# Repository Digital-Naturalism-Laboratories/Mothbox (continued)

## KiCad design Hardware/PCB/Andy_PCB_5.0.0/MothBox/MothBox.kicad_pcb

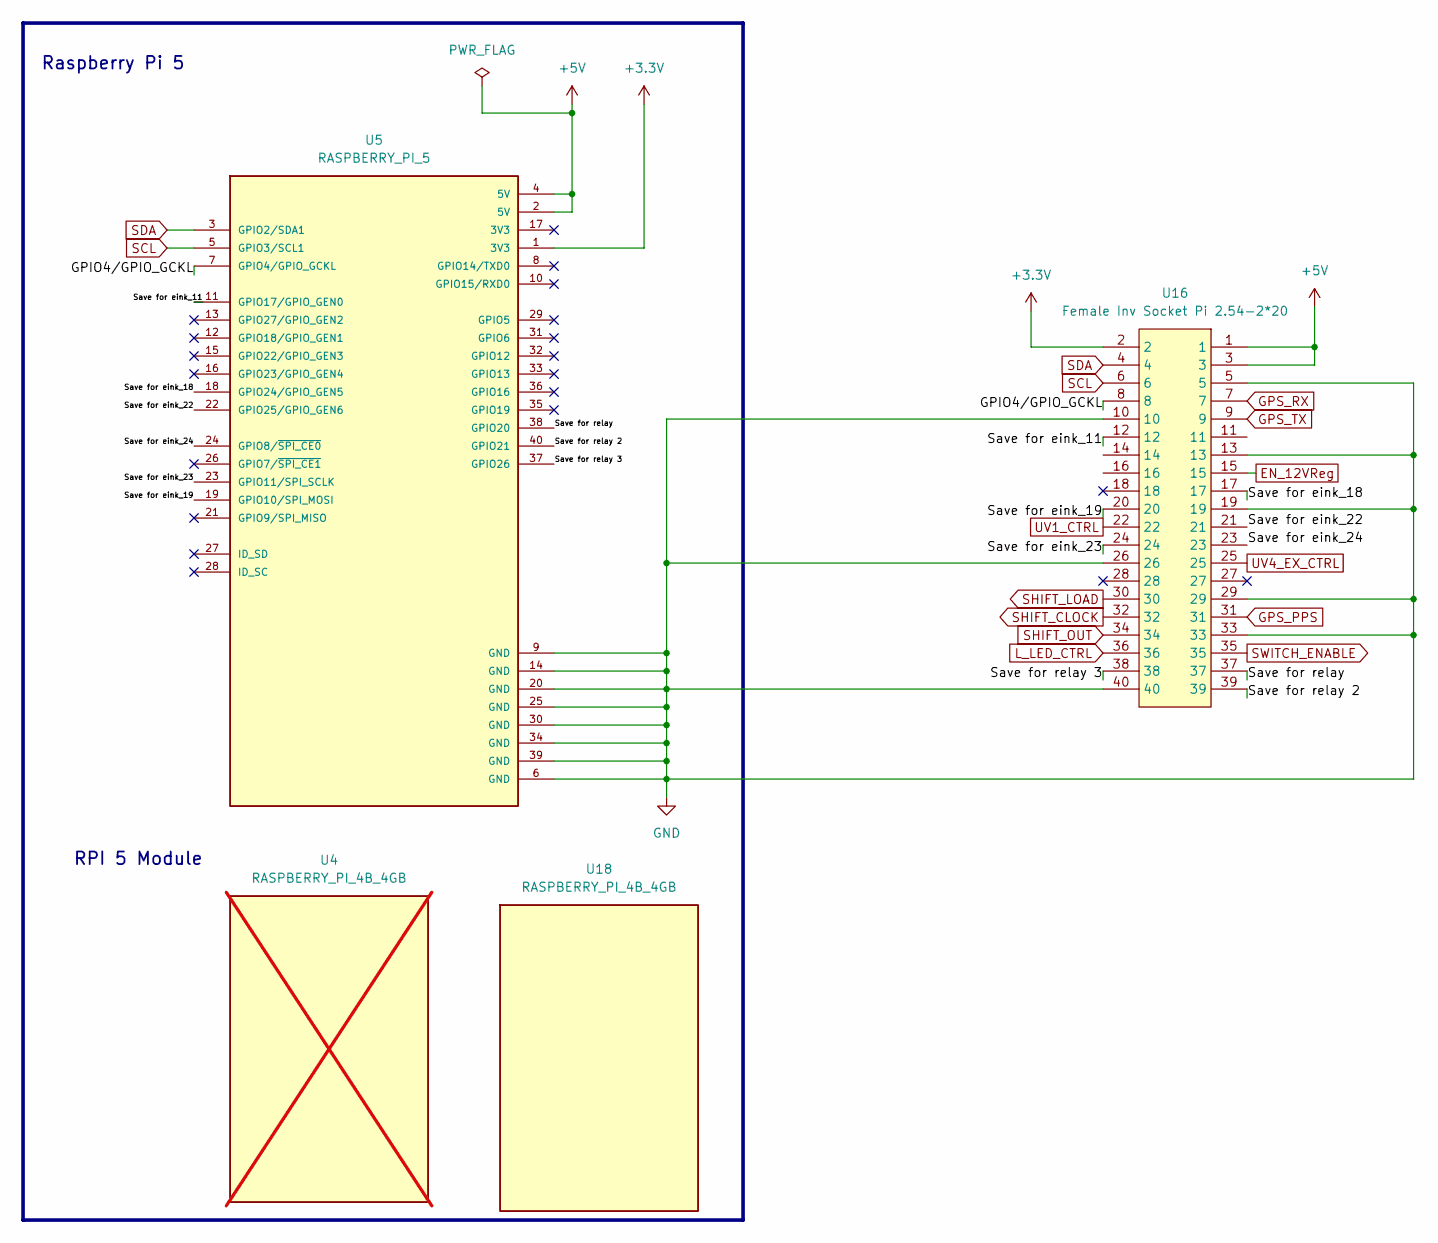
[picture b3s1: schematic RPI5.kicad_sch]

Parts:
U4: RASPBERRY_PI_4B_4GB; MODULE_RASPBERRY_PI_4B_4GB; PARTREV 4; Digikey Part No SC1113; not fitted
U5: RASPBERRY_PI_5; EPAPER_PinHeader_2x20_P2.54mm_Vertical; LCSC Part no C5224014
U16: Female Inv Socket Pi 2.54-2*20; HDR-TH_40P-P2.54-H-F-R2-C20-W8.5; LCSC Part C2897440
U18: RASPBERRY_PI_4B_4GB; MODULE_RASPBERRY_PI_4B_4GB_Sideways; PARTREV 4; Digikey Part No SC1113

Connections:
+3.3V: U5.1 (3V3), U16.2; also elsewhere on the board
+5V: U5.2 (5V), U5.4 (5V), U16.1, U16.3; also elsewhere on the board
/RPI5/GPIO4/GPIO_GCKL: U5.7 (GPIO4/GPIO_GCKL), U16.8
/RPI5/Save for eink_11: U5.11 (GPIO17/GPIO_GEN0), U16.12
/RPI5/Save for eink_18: U5.18 (GPIO24/GPIO_GEN5), U16.17
/RPI5/Save for eink_19: U5.19 (GPIO10/SPI_MOSI), U16.20
/RPI5/Save for eink_22: U5.22 (GPIO25/GPIO_GEN6), U16.21
/RPI5/Save for eink_23: U5.23 (GPIO11/SPI_SCLK), U16.24
/RPI5/Save for eink_24: U5.24 (GPIO8/~SPI_CE0), U16.23
/RPI5/Save for relay: U5.38 (GPIO20), U16.37
/RPI5/Save for relay 2: U5.40 (GPIO21), U16.39
/RPI5/Save for relay 3: U5.37 (GPIO26), U16.38
EN_12VReg: U16.15; also elsewhere on the board
GND: U5.6 (GND), U5.9 (GND), U5.14 (GND), U5.20 (GND), U5.25 (GND), U5.30 (GND), U5.34 (GND), U5.39 (GND), U16.5, U16.10, U16.13, U16.19, U16.26, U16.29, U16.33, U16.40; also elsewhere on the board
GPS_PPS: U16.31; also elsewhere on the board
GPS_RX: U16.7; also elsewhere on the board
GPS_TX: U16.9; also elsewhere on the board
L_LED_CTRL: U16.36; also elsewhere on the board
SCL: U5.5 (GPIO3/SCL1), U16.6; also elsewhere on the board
SDA: U5.3 (GPIO2/SDA1), U16.4; also elsewhere on the board
SHIFT_CLOCK: U16.32; also elsewhere on the board
SHIFT_LOAD: U16.30; also elsewhere on the board
SHIFT_OUT: U16.34; also elsewhere on the board
SWITCH_ENABLE: U16.35; also elsewhere on the board
UV1_CTRL: U16.22; also elsewhere on the board
UV4_EX_CTRL: U16.25; also elsewhere on the board

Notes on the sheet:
RPI 5 Module
Raspberry Pi 5

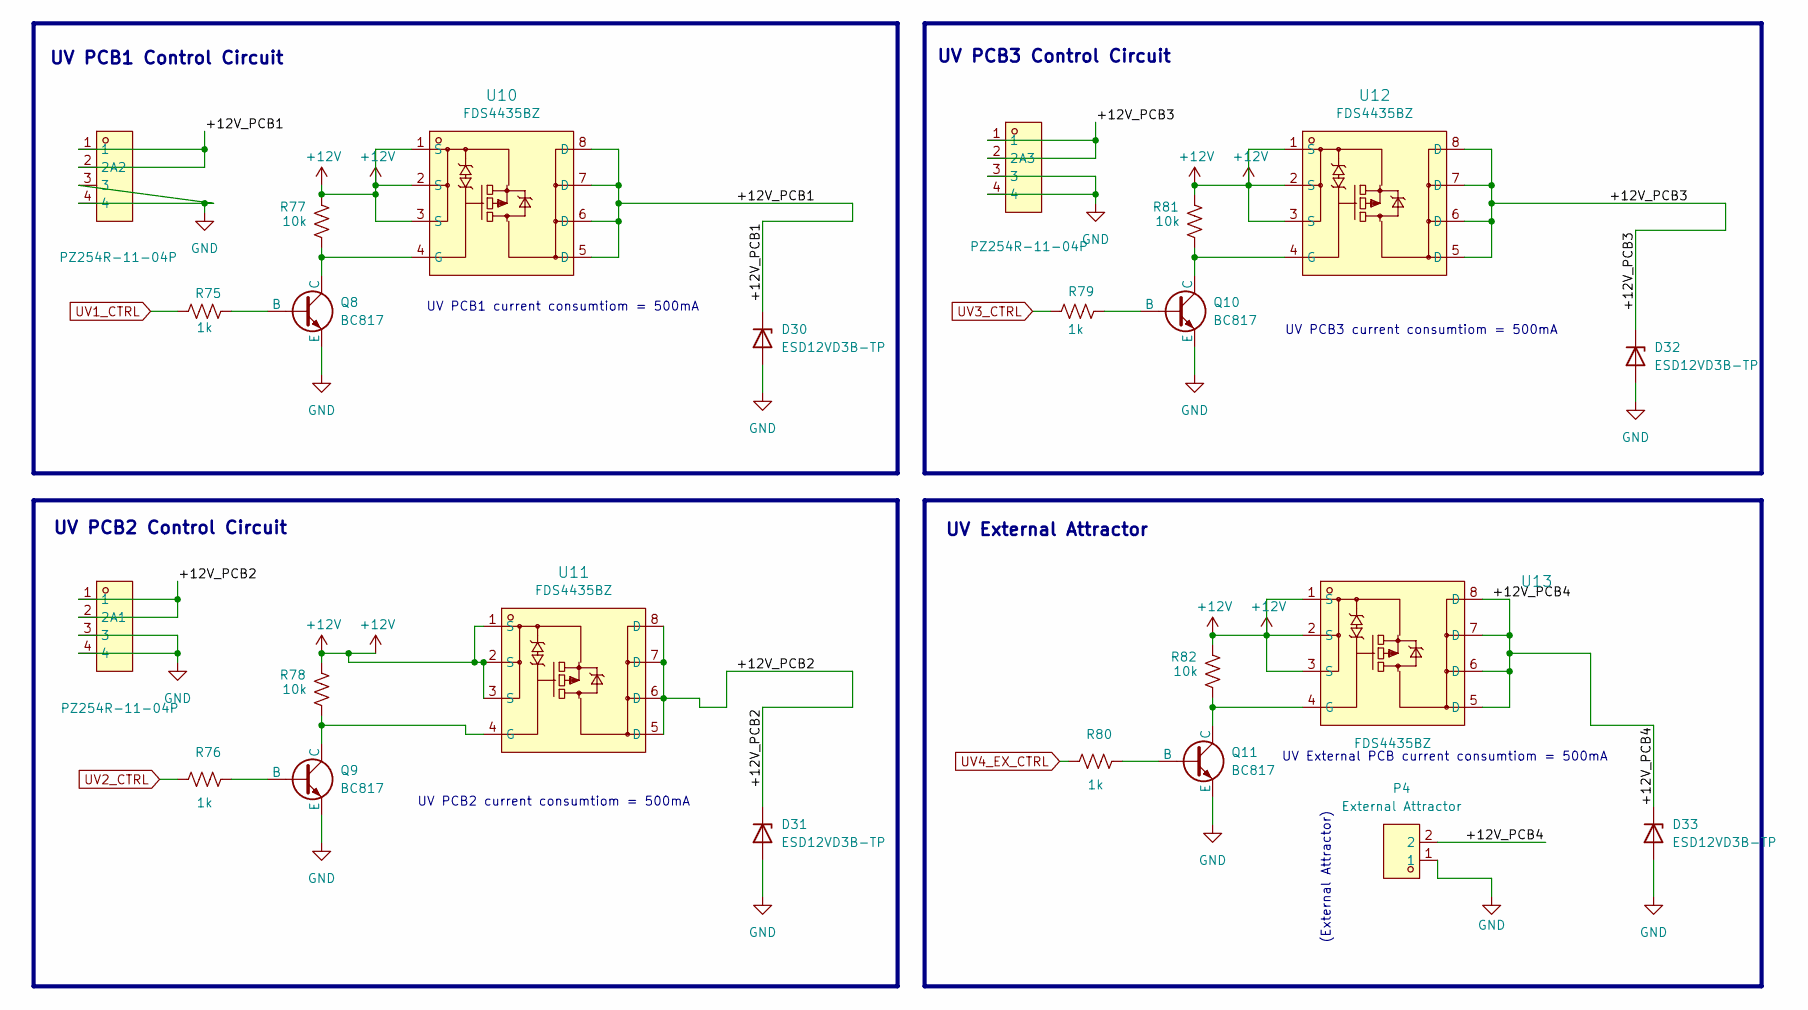
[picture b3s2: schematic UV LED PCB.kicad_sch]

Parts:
A1, A2, A3: PZ254R-11-04P; HDR-TH_4P-P2.54-H-M-W10.4; LCSC Part C492412
D30, D31, D32, D33: ESD12VD3B-TP; D_SOD-323; LCSC Part no C435886
P4: External Attractor; CONN-TH_2P-P5.08_DIBO_DB142R-5.08-2P; LCSC Part C2898709
Q8, Q9, Q10, Q11: BC817; SOT-23; LCSC Part no C39828
R75, R76, R79, R80: 1k; R_0805_2012Metric; LCSC Part no C95781
R77, R78, R81, R82: 10k; R_0805_2012Metric; LCSC Part no C84376
U10, U11, U12, U13: FDS4435BZ; SOIC-8_L5.0-W4.0-P1.27-LS6.0-BL; LCSC Part C23931

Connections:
+12V: R77.2, R78.2, R81.2, R82.2, U10.1 (S), U10.2 (S), U10.3 (S), U11.1 (S), U11.2 (S), U11.3 (S), U12.1 (S), U12.2 (S), U12.3 (S), U13.1 (S), U13.2 (S), U13.3 (S); also elsewhere on the board
/UV LED PCB/+12V_PCB1: A2.1, A2.2, D30.1 (K), U10.5 (D), U10.6 (D), U10.7 (D), U10.8 (D)
/UV LED PCB/+12V_PCB2: A1.1, A1.2, D31.1 (K), U11.5 (D), U11.6 (D), U11.7 (D), U11.8 (D)
/UV LED PCB/+12V_PCB3: A3.1, A3.2, D32.1 (K), U12.5 (D), U12.6 (D), U12.7 (D), U12.8 (D)
/UV LED PCB/+12V_PCB4: D33.1 (K), P4.2, U13.5 (D), U13.6 (D), U13.7 (D), U13.8 (D)
GND: A1.3, A1.4, A2.3, A2.4, A3.3, A3.4, D30.2 (A), D31.2 (A), D32.2 (A), D33.2 (A), P4.1, Q8.2 (E), Q9.2 (E), Q10.2 (E), Q11.2 (E); also elsewhere on the board
unnamed: Q8.1 (B), R75.1
unnamed: Q8.3 (C), R77.1, U10.4 (G)
unnamed: Q9.1 (B), R76.1
unnamed: Q9.3 (C), R78.1, U11.4 (G)
unnamed: Q10.1 (B), R79.1
unnamed: Q10.3 (C), R81.1, U12.4 (G)
unnamed: Q11.1 (B), R80.1
unnamed: Q11.3 (C), R82.1, U13.4 (G)
UV1_CTRL: R75.2; also elsewhere on the board
UV2_CTRL: R76.2
UV3_CTRL: R79.2
UV4_EX_CTRL: R80.2; also elsewhere on the board

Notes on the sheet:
UV External Attractor
(External Attractor)
UV PCB1 Control Circuit
UV PCB3 Control Circuit
UV PCB1 current consumtiom = 500mA
UV PCB2 current consumtiom = 500mA
UV PCB3 current consumtiom = 500mA
UV PCB2 Control Circuit
UV External PCB current consumtiom = 500mA

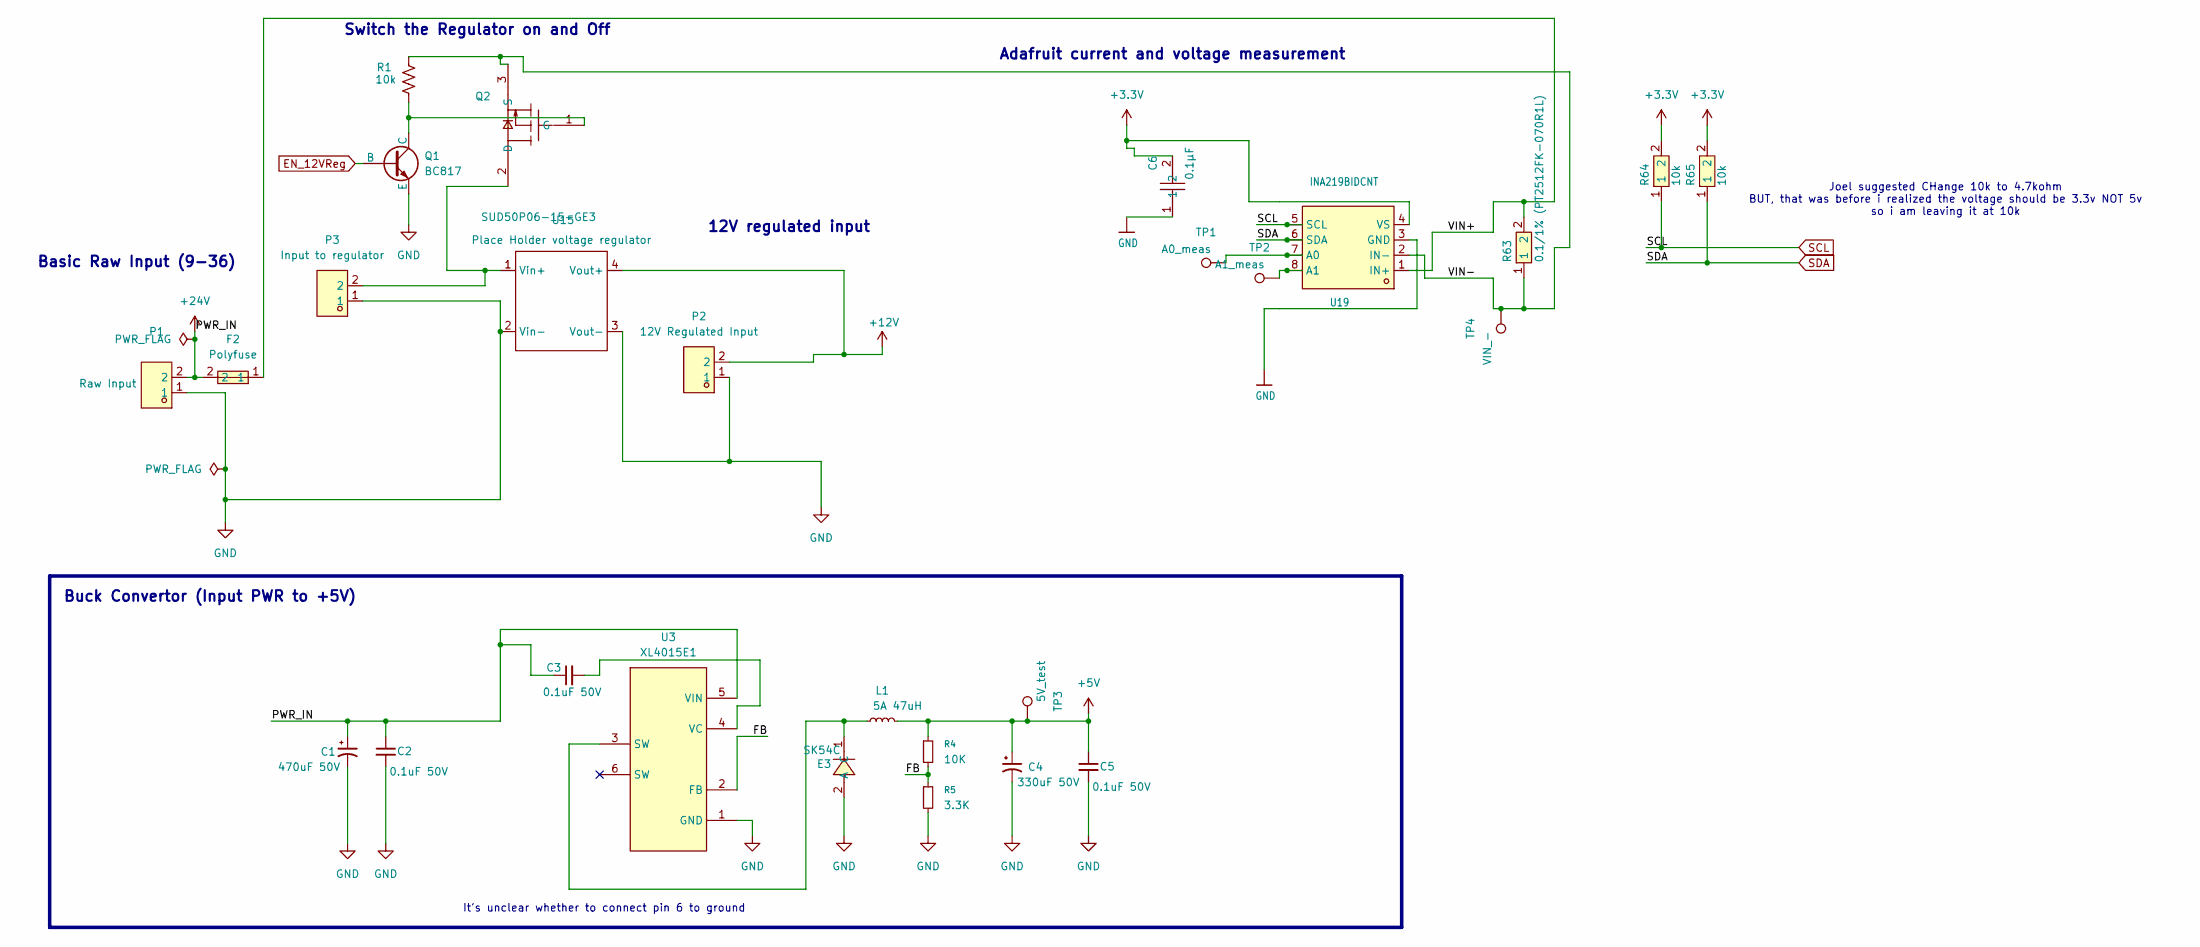
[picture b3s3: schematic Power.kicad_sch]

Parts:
C1: 470uF 50V; CP_Elec_10x12.5; LCSC Part no C90272
C2, C3, C5: 0.1uF 50V; C_0805_2012Metric_Pad1.18x1.45mm_HandSolder; LCSC Part no C3011704
C4: 330uF 50V; CP_Elec_10x10; LCSC Part no C2687701
C6: 0.1µF; C0603; LCSC Part C14663
E3: SK54C; SMC_L6.9-W5.9-LS8.0-RD; PARTREV S2311; LCSC Part no C5449119
F2: Polyfuse; F0805; LCSC Part C22435897
L1: 5A 47uH; L_Chilisin_BMRG00131360; LCSC Part no C497913
P1: Raw Input; CONN-TH_2P-P5.08_DIBO_DB142R-5.08-2P; LCSC Part C2898709
P2: 12V Regulated Input; CONN-TH_2P-P5.08_DIBO_DB142R-5.08-2P; LCSC Part C2898709
P3: Input to regulator; CONN-TH_2P-P5.08_DIBO_DB142R-5.08-2P; LCSC Part C2898709
Q1: BC817; SOT-23; LCSC Part no C39828
Q2: SUD50P06-15-GE3; TO-252-3_L6.5-W5.8-P4.58-BL; LCSC Part C141584
R1: 10k; R_0805_2012Metric; LCSC Part no C84376
R4: 10K; C_0805_2012Metric_Pad1.18x1.45mm_HandSolder; LCSC Part no C84376
R5: 3.3K; C_0805_2012Metric_Pad1.18x1.45mm_HandSolder; LCSC Part no C114531
R63: 0.1/1% (PT2512FK-070R1L); R2512; LCSC Part C23067426
R64, R65: 10k; R0603; LCSC Part C2930027
TP1: A0_meas; TestPoint_THTPad_D1.0mm_Drill0.5mm
TP2: A1_meas; TestPoint_THTPad_D1.0mm_Drill0.5mm
TP3: 5V_test; TestPoint_THTPad_D1.0mm_Drill0.5mm
TP4: VIN_-; TestPoint_THTPad_D1.0mm_Drill0.5mm
U3: XL4015E1; TO-263-5_L10.2-W8.9-P1.70-TL; PARTREV 1.5; LCSC Part no C51661
U15: Place Holder voltage regulator
U19: INA219BIDCNT; SOT-23-8_L3.0-W1.7-P0.65-LS2.8-BR; LCSC Part C87469

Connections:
+3.3V: C6.2, R64.2, R65.2, U19.4 (VS); also elsewhere on the board
+5V: C4.1, C5.1, L1.2, R4.1, TP3.1; also elsewhere on the board
+12V: P2.2, U15.4 (Vout+); also elsewhere on the board
+24V: C1.1, C2.1, C3.1, F2.2, P1.2, U3.5 (VIN)
/Power/FB: R4.2, R5.1, U3.2 (FB)
/Power/VIN+: F2.1, R63.2, U19.1 (IN+)
/Power/VIN-: Q2.3 (S), R1.2, R63.1, TP4.1, U19.2 (IN-)
EN_12VReg: Q1.1 (B); also elsewhere on the board
GND: C1.2, C2.2, C4.2, C5.2, C6.1, E3.2 (A), P1.1, P2.1, P3.1, Q1.2 (E), R5.2, U3.1 (GND), U15.2 (Vin-), U15.3 (Vout-), U19.3 (GND); also elsewhere on the board
unnamed: E3.1 (C), L1.1, U3.3 (SW)
unnamed: Q1.3 (C), Q2.1 (G), R1.1
unnamed: P3.2, Q2.2 (D), U15.1 (Vin+)
unnamed: C3.2, U3.4 (VC)
unnamed: TP1.1, U19.7 (A0)
unnamed: TP2.1, U19.8 (A1)
SCL: R64.1, U19.5 (SCL); also elsewhere on the board
SDA: R65.1, U19.6 (SDA); also elsewhere on the board

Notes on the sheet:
Adafruit current and voltage measurement
Buck Convertor (Input PWR to +5V)
It's unclear whether to connect pin 6 to ground
Joel suggested CHange 10k to 4.7kohm BUT, that was before i realized the voltage should be 3.3v NOT 5v so i am leaving it at 10k
12V regulated input
Switch the Regulator on and Off
Basic Raw Input (9-36)

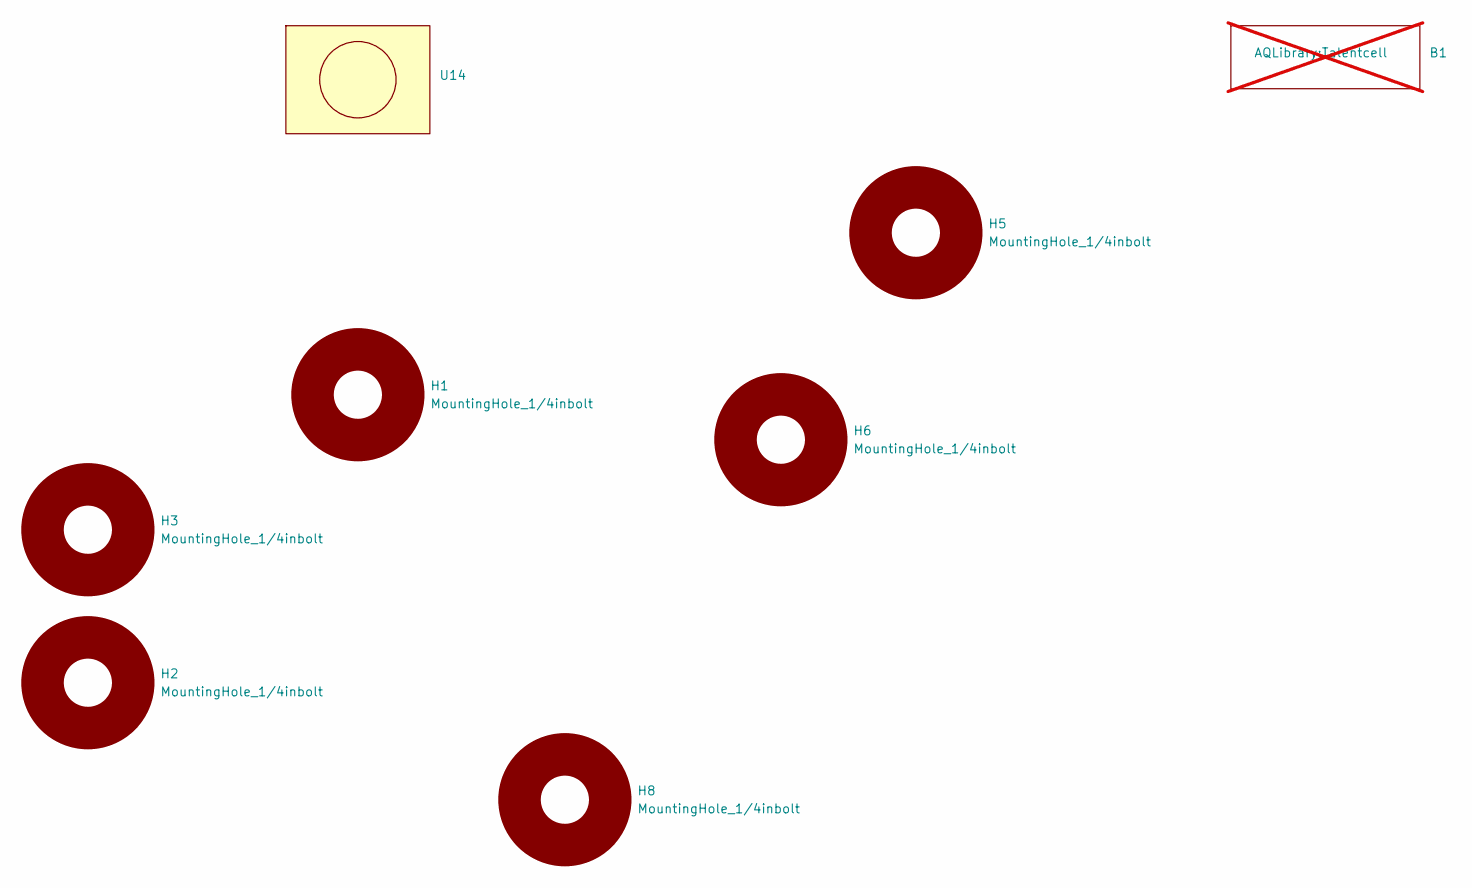
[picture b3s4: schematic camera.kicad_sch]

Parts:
B1: Talentcell; not fitted
H1, H2, H3, H5, H6, H8: MountingHole_1/4inbolt; MountingHole_6.4mm_M6_Pad
U14: Arducam Owlsight

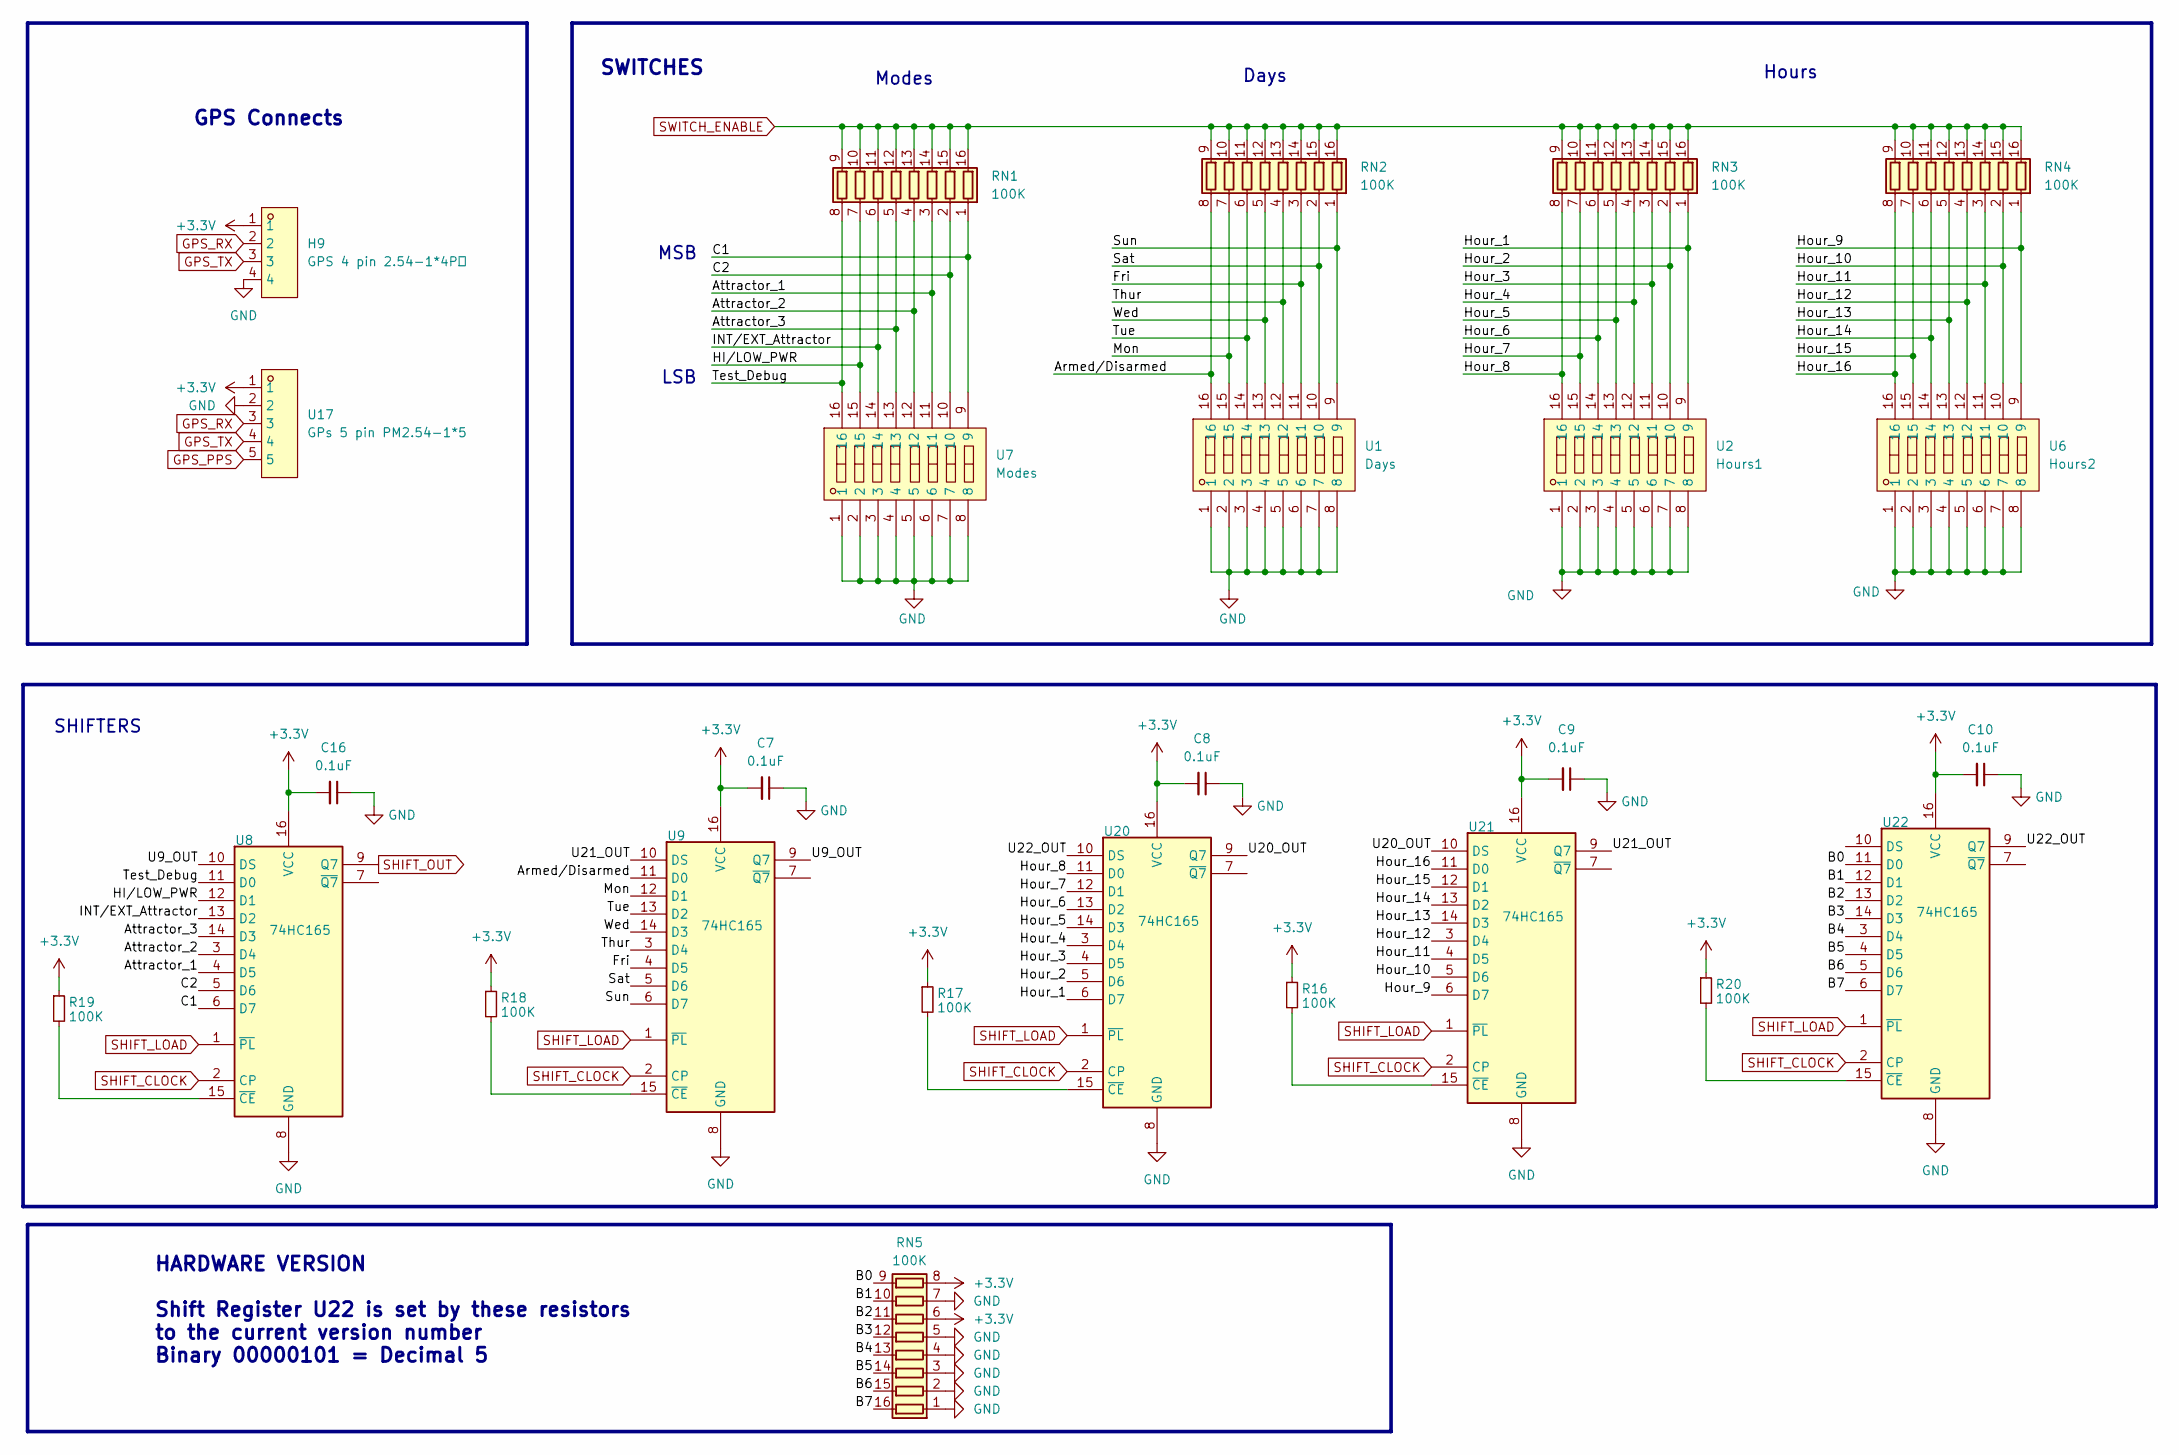
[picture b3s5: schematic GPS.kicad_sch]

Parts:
C7, C8, C9, C10, C16: 0.1uF; C_0805_2012Metric; Digikey Part No 311-1140-2-ND
H9: GPS 4 pin 2.54-1*4P母; GPS4pin_HDR-TH_4P-P2.54-V-F; LCSC Part C2718488
R16, R17, R18, R19, R20: 100K; R_0603_1608Metric
RN1, RN2, RN3, RN4, RN5: 100K; 16P8-R-Array
U1: Days; SW-SMD_SMXS-08K-TP; LCSC Part C5439767
U2: Hours1; SW-SMD_SMXS-08K-TP; LCSC Part C5439767
U6: Hours2; SW-SMD_SMXS-08K-TP; LCSC Part C5439767
U7: Modes; SW-SMD_SMXS-08K-TP; LCSC Part C5439767
U8, U9, U20, U21, U22: 74HC165; SOIC-16_3.9x9.9mm_P1.27mm
U17: GPs 5 pin PM2.54-1*5; GPS5pin_HDR-TH_5P-P2.54-V-F; LCSC Part C5116488

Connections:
+3.3V: C7.2, C8.2, C9.2, C10.2, C16.2, H9.1, R16.1, R17.1, R18.1, R19.1, R20.1, RN5.6 (R6.1), RN5.8 (R8.1), U8.16 (VCC), U9.16 (VCC), U17.1, U20.16 (VCC), U21.16 (VCC), U22.16 (VCC); also elsewhere on the board
/GPS and Switches/Armed/Disarmed: RN2.8 (R8.1), U1.16, U9.11 (D0)
/GPS and Switches/Attractor_1: RN1.3 (R3.1), U7.11, U8.4 (D5)
/GPS and Switches/Attractor_2: RN1.4 (R4.1), U7.12, U8.3 (D4)
/GPS and Switches/Attractor_3: RN1.5 (R5.1), U7.13, U8.14 (D3)
/GPS and Switches/B0: RN5.9 (R8.2), U22.11 (D0)
/GPS and Switches/B1: RN5.10 (R7.2), U22.12 (D1)
/GPS and Switches/B2: RN5.11 (R6.2), U22.13 (D2)
/GPS and Switches/B3: RN5.12 (R5.2), U22.14 (D3)
/GPS and Switches/B4: RN5.13 (R4.2), U22.3 (D4)
/GPS and Switches/B5: RN5.14 (R3.2), U22.4 (D5)
/GPS and Switches/B6: RN5.15 (R2.2), U22.5 (D6)
/GPS and Switches/B7: RN5.16 (R1.2), U22.6 (D7)
/GPS and Switches/C1: RN1.1 (R1.1), U7.9, U8.6 (D7)
/GPS and Switches/C2: RN1.2 (R2.1), U7.10, U8.5 (D6)
/GPS and Switches/Fri: RN2.3 (R3.1), U1.11, U9.4 (D5)
/GPS and Switches/HI/LOW_PWR: RN1.7 (R7.1), U7.15, U8.12 (D1)
/GPS and Switches/Hour_1: RN3.1 (R1.1), U2.9, U20.6 (D7)
/GPS and Switches/Hour_2: RN3.2 (R2.1), U2.10, U20.5 (D6)
/GPS and Switches/Hour_3: RN3.3 (R3.1), U2.11, U20.4 (D5)
/GPS and Switches/Hour_4: RN3.4 (R4.1), U2.12, U20.3 (D4)
/GPS and Switches/Hour_5: RN3.5 (R5.1), U2.13, U20.14 (D3)
/GPS and Switches/Hour_6: RN3.6 (R6.1), U2.14, U20.13 (D2)
/GPS and Switches/Hour_7: RN3.7 (R7.1), U2.15, U20.12 (D1)
/GPS and Switches/Hour_8: RN3.8 (R8.1), U2.16, U20.11 (D0)
/GPS and Switches/Hour_9: RN4.1 (R1.1), U6.9, U21.6 (D7)
/GPS and Switches/Hour_10: RN4.2 (R2.1), U6.10, U21.5 (D6)
/GPS and Switches/Hour_11: RN4.3 (R3.1), U6.11, U21.4 (D5)
/GPS and Switches/Hour_12: RN4.4 (R4.1), U6.12, U21.3 (D4)
/GPS and Switches/Hour_13: RN4.5 (R5.1), U6.13, U21.14 (D3)
/GPS and Switches/Hour_14: RN4.6 (R6.1), U6.14, U21.13 (D2)
/GPS and Switches/Hour_15: RN4.7 (R7.1), U6.15, U21.12 (D1)
/GPS and Switches/Hour_16: RN4.8 (R8.1), U6.16, U21.11 (D0)
/GPS and Switches/INT/EXT_Attractor: RN1.6 (R6.1), U7.14, U8.13 (D2)
/GPS and Switches/Mon: RN2.7 (R7.1), U1.15, U9.12 (D1)
/GPS and Switches/Sat: RN2.2 (R2.1), U1.10, U9.5 (D6)
/GPS and Switches/Sun: RN2.1 (R1.1), U1.9, U9.6 (D7)
/GPS and Switches/Test_Debug: RN1.8 (R8.1), U7.16, U8.11 (D0)
/GPS and Switches/Thur: RN2.4 (R4.1), U1.12, U9.3 (D4)
/GPS and Switches/Tue: RN2.6 (R6.1), U1.14, U9.13 (D2)
/GPS and Switches/U9_OUT: U8.10 (DS), U9.9 (Q7)
/GPS and Switches/U20_OUT: U20.9 (Q7), U21.10 (DS)
/GPS and Switches/U21_OUT: U9.10 (DS), U21.9 (Q7)
/GPS and Switches/U22_OUT: U20.10 (DS), U22.9 (Q7)
/GPS and Switches/Wed: RN2.5 (R5.1), U1.13, U9.14 (D3)
GND: C7.1, C8.1, C9.1, C10.1, C16.1, H9.4, RN5.1 (R1.1), RN5.2 (R2.1), RN5.3 (R3.1), RN5.4 (R4.1), RN5.5 (R5.1), RN5.7 (R7.1), U1.1, U1.2, U1.3, U1.4, U1.5, U1.6, U1.7, U1.8, U2.1, U2.2, U2.3, U2.4, U2.5, U2.6, U2.7, U2.8, U6.1, U6.2, U6.3, U6.4, U6.5, U6.6, U6.7, U6.8, U7.1, U7.2, U7.3, U7.4, U7.5, U7.6, U7.7, U7.8, U8.8 (GND), U9.8 (GND), U17.2, U20.8 (GND), U21.8 (GND), U22.8 (GND); also elsewhere on the board
GPS_PPS: U17.5; also elsewhere on the board
GPS_RX: H9.2, U17.3; also elsewhere on the board
GPS_TX: H9.3, U17.4; also elsewhere on the board
unnamed: R19.2, U8.15 (~CE)
unnamed: R18.2, U9.15 (~CE)
unnamed: R17.2, U20.15 (~CE)
unnamed: R16.2, U21.15 (~CE)
unnamed: R20.2, U22.15 (~CE)
SHIFT_CLOCK: U8.2 (CP), U9.2 (CP), U20.2 (CP), U21.2 (CP), U22.2 (CP); also elsewhere on the board
SHIFT_LOAD: U8.1 (~PL), U9.1 (~PL), U20.1 (~PL), U21.1 (~PL), U22.1 (~PL); also elsewhere on the board
SHIFT_OUT: U8.9 (Q7); also elsewhere on the board
SWITCH_ENABLE: RN1.9 (R8.2), RN1.10 (R7.2), RN1.11 (R6.2), RN1.12 (R5.2), RN1.13 (R4.2), RN1.14 (R3.2), RN1.15 (R2.2), RN1.16 (R1.2), RN2.9 (R8.2), RN2.10 (R7.2), RN2.11 (R6.2), RN2.12 (R5.2), RN2.13 (R4.2), RN2.14 (R3.2), RN2.15 (R2.2), RN2.16 (R1.2), RN3.9 (R8.2), RN3.10 (R7.2), RN3.11 (R6.2), RN3.12 (R5.2), RN3.13 (R4.2), RN3.14 (R3.2), RN3.15 (R2.2), RN3.16 (R1.2), RN4.9 (R8.2), RN4.10 (R7.2), RN4.11 (R6.2), RN4.12 (R5.2), RN4.13 (R4.2), RN4.14 (R3.2), RN4.15 (R2.2), RN4.16 (R1.2); also elsewhere on the board

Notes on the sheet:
LSB
HARDWARE VERSION Shift Register U22 is set by these resistors to the current version number Binary 00000101 = Decimal 5
SWITCHES
GPS Connects
MSB
Days
Modes
SHIFTERS
Hours

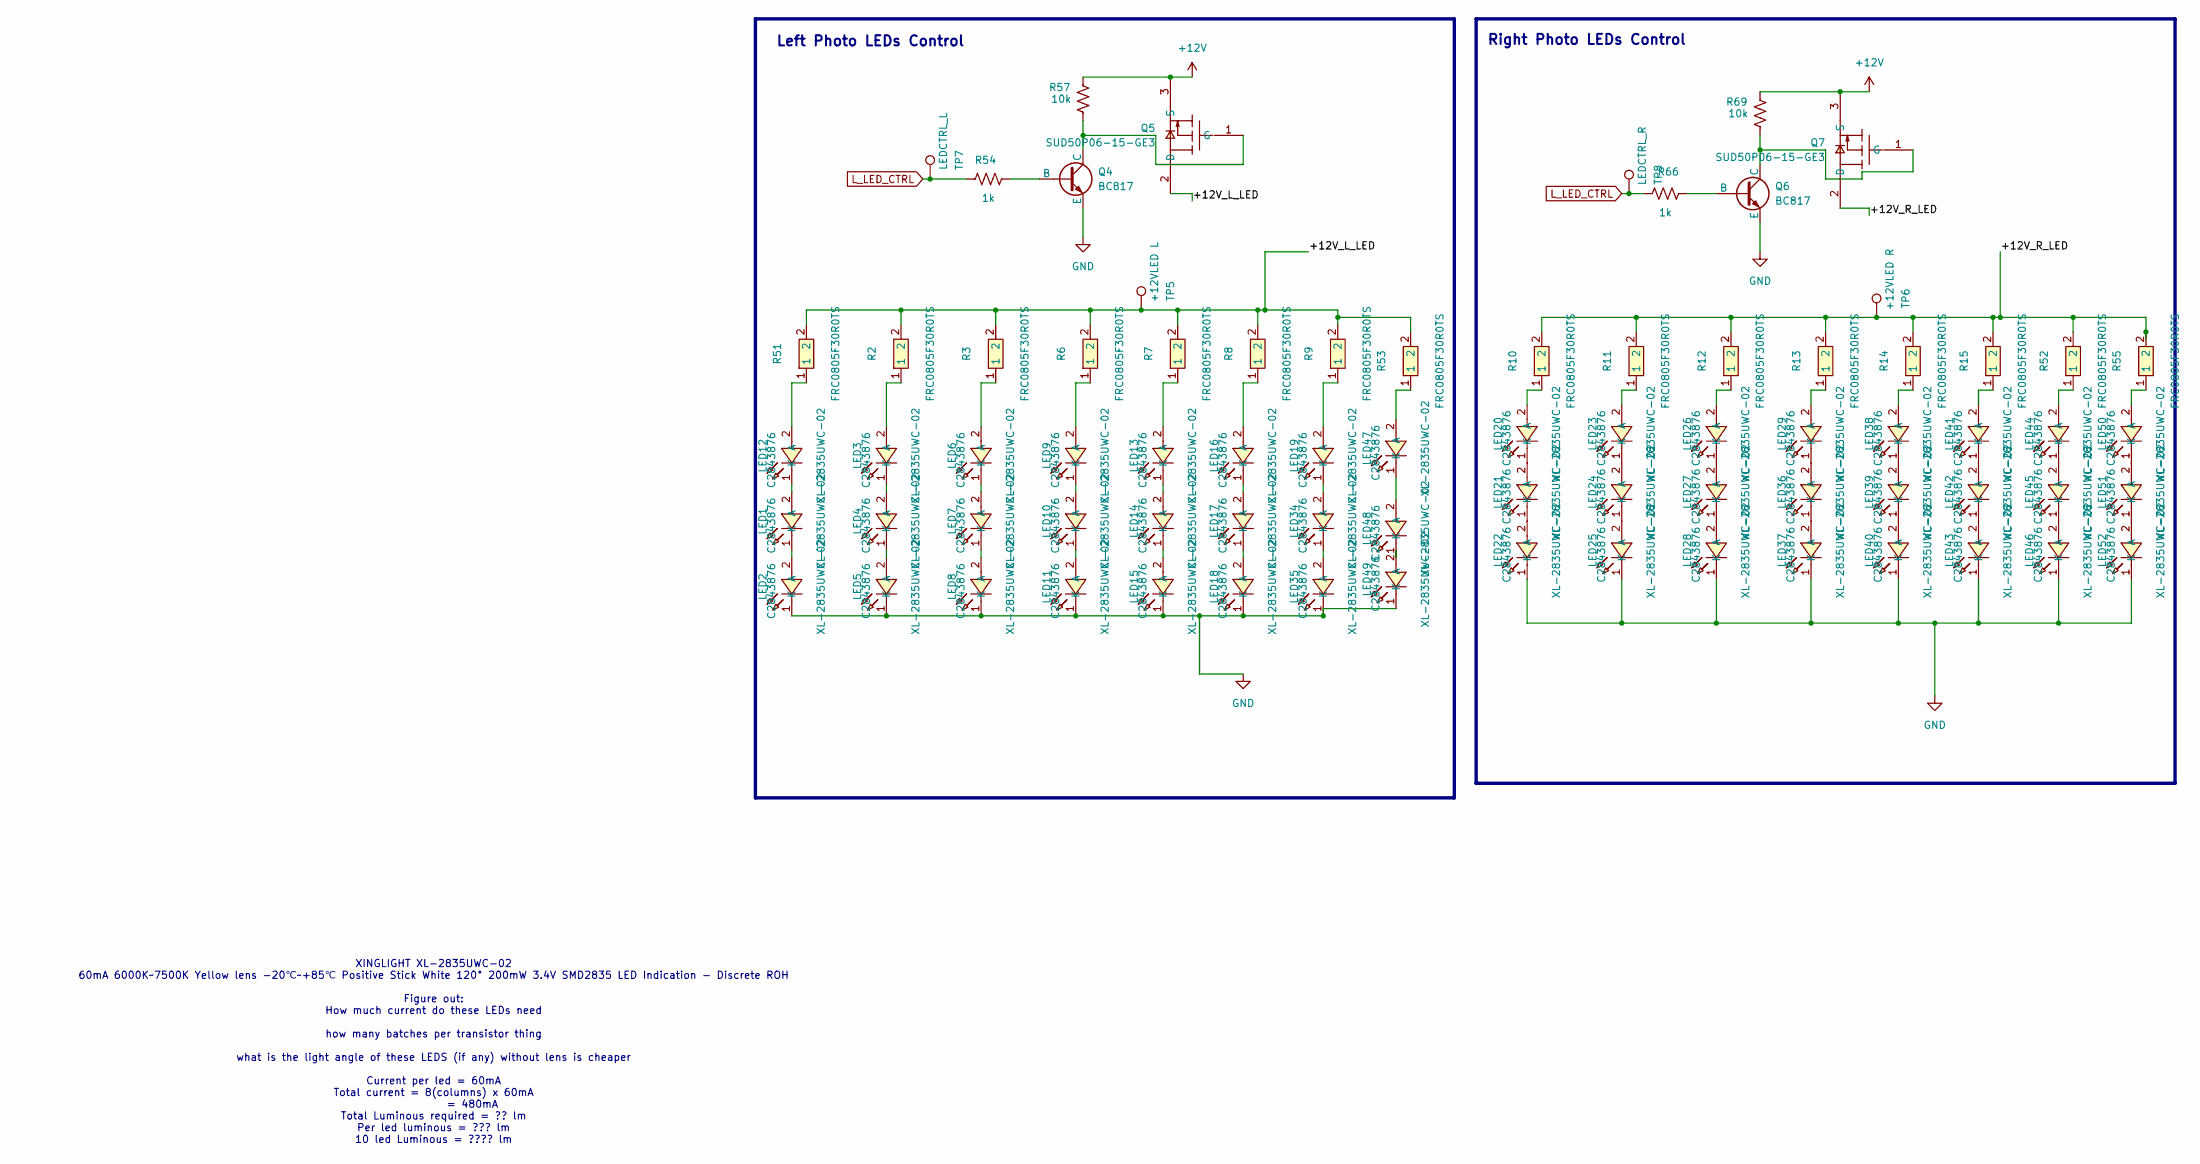
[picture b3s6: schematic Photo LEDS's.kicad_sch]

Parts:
LED1, LED2, LED3, LED4, LED5, LED6, LED7, LED8, LED9, LED10, LED11, LED12, LED13, LED14, LED15, LED16, LED17, LED18, LED19, LED20, LED21, LED22, LED23, LED24, LED25, LED26, LED27, LED28, LED29, LED34, LED35, LED36, LED37, LED38, LED39, LED40, LED41, LED42, LED43, LED44, LED45, LED46, LED47, LED48, LED49, LED50, LED51, LED52: XL-2835UWC-02; LED-SMD_L3.5-W2.8-RD_1.25T-2PWT; LCSC Part no C2843876
Q4, Q6: BC817; SOT-23; LCSC Part no C39828
Q5, Q7: SUD50P06-15-GE3; TO-252-3_L6.5-W5.8-P4.58-BL; LCSC Part C141584
R2, R3, R6, R7, R8, R9, R10, R11, R12, R13, R14, R15, R51, R52, R53, R55: FRC0805F30R0TS; R0805; LCSC Part C2907256
R54, R66: 1k; R_0805_2012Metric; LCSC Part no C95781
R57, R69: 10k; R_0805_2012Metric; LCSC Part no C84376
TP5: +12VLED L; TestPoint_THTPad_D1.0mm_Drill0.5mm
TP6: +12VLED R; TestPoint_THTPad_D1.0mm_Drill0.5mm
TP7: LEDCTRL_L; TestPoint_THTPad_D1.0mm_Drill0.5mm
TP8: LEDCTRL_R; TestPoint_THTPad_D1.0mm_Drill0.5mm

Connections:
+12V: Q5.3 (S), Q7.3 (S), R57.2, R69.2; also elsewhere on the board
/Photo LED's/+12V_L_LED: Q5.2 (D), R2.2, R3.2, R6.2, R7.2, R8.2, R9.2, R51.2, R53.2, TP5.1
/Photo LED's/+12V_R_LED: Q7.2 (D), R10.2, R11.2, R12.2, R13.2, R14.2, R15.2, R52.2, R55.2, TP6.1
GND: LED2.1 (K), LED5.1 (K), LED8.1 (K), LED11.1 (K), LED15.1 (K), LED18.1 (K), LED22.1 (K), LED25.1 (K), LED28.1 (K), LED35.1 (K), LED37.1 (K), LED40.1 (K), LED43.1 (K), LED46.1 (K), LED49.1 (K), LED52.1 (K), Q4.2 (E), Q6.2 (E); also elsewhere on the board
L_LED_CTRL: R54.2, R66.2, TP7.1, TP8.1; also elsewhere on the board
unnamed: LED1.2 (A), LED12.1 (K)
unnamed: LED1.1 (K), LED2.2 (A)
unnamed: LED3.2 (A), R2.1
unnamed: LED3.1 (K), LED4.2 (A)
unnamed: LED4.1 (K), LED5.2 (A)
unnamed: LED6.2 (A), R3.1
unnamed: LED6.1 (K), LED7.2 (A)
unnamed: LED7.1 (K), LED8.2 (A)
unnamed: LED9.2 (A), R6.1
unnamed: LED9.1 (K), LED10.2 (A)
unnamed: LED10.1 (K), LED11.2 (A)
unnamed: LED12.2 (A), R51.1
unnamed: LED13.2 (A), R7.1
unnamed: LED13.1 (K), LED14.2 (A)
unnamed: LED14.1 (K), LED15.2 (A)
unnamed: LED16.2 (A), R8.1
unnamed: LED16.1 (K), LED17.2 (A)
unnamed: LED17.1 (K), LED18.2 (A)
unnamed: LED19.2 (A), R9.1
unnamed: LED19.1 (K), LED34.2 (A)
unnamed: LED20.2 (A), R10.1
unnamed: LED20.1 (K), LED21.2 (A)
unnamed: LED21.1 (K), LED22.2 (A)
unnamed: LED23.2 (A), R11.1
unnamed: LED23.1 (K), LED24.2 (A)
unnamed: LED24.1 (K), LED25.2 (A)
unnamed: LED26.2 (A), R12.1
unnamed: LED26.1 (K), LED27.2 (A)
unnamed: LED27.1 (K), LED28.2 (A)
unnamed: LED29.2 (A), R13.1
unnamed: LED29.1 (K), LED36.2 (A)
unnamed: LED34.1 (K), LED35.2 (A)
unnamed: LED36.1 (K), LED37.2 (A)
unnamed: LED38.2 (A), R14.1
unnamed: LED38.1 (K), LED39.2 (A)
unnamed: LED39.1 (K), LED40.2 (A)
unnamed: LED41.2 (A), R15.1
unnamed: LED41.1 (K), LED42.2 (A)
unnamed: LED42.1 (K), LED43.2 (A)
unnamed: LED44.2 (A), R52.1
unnamed: LED44.1 (K), LED45.2 (A)
unnamed: LED45.1 (K), LED46.2 (A)
unnamed: LED47.2 (A), R53.1
unnamed: LED47.1 (K), LED48.2 (A)
unnamed: LED48.1 (K), LED49.2 (A)
unnamed: LED50.2 (A), R55.1
unnamed: LED50.1 (K), LED51.2 (A)
unnamed: LED51.1 (K), LED52.2 (A)
unnamed: Q4.1 (B), R54.1
unnamed: Q4.3 (C), Q5.1 (G), R57.1
unnamed: Q6.1 (B), R66.1
unnamed: Q6.3 (C), Q7.1 (G), R69.1

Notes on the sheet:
XINGLIGHT XL-2835UWC-02 60mA 6000K~7500K Yellow lens -20℃~+85℃ Positive Stick White 120° 200mW 3.4V SMD2835 LED Indication - Discrete ROH Figure out: How much current do these LEDs need how many batches per transistor thing what is the light angle of these LEDS (if any) without lens is cheaper Curr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
Right Photo LEDs Control
Left Photo LEDs Control
